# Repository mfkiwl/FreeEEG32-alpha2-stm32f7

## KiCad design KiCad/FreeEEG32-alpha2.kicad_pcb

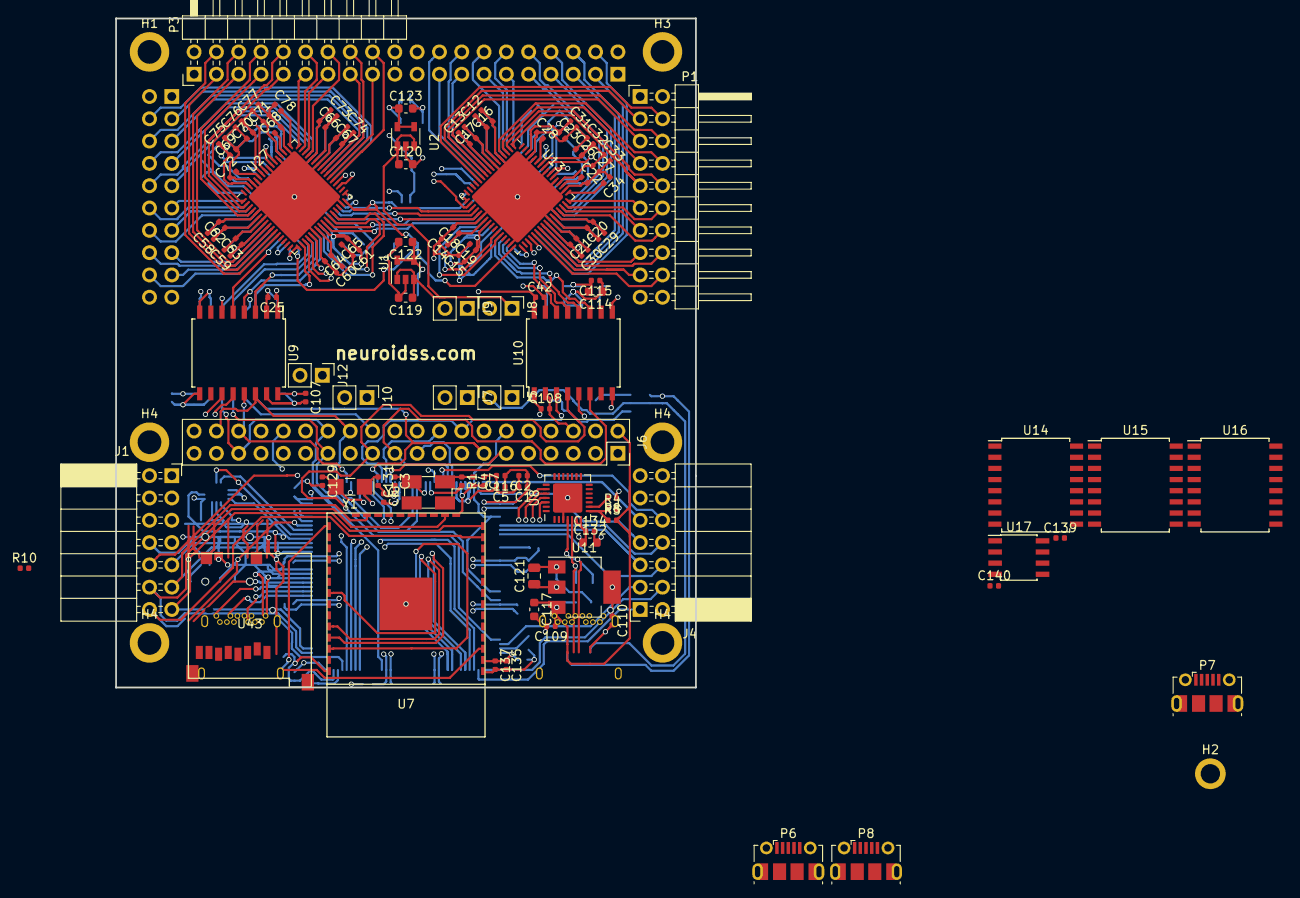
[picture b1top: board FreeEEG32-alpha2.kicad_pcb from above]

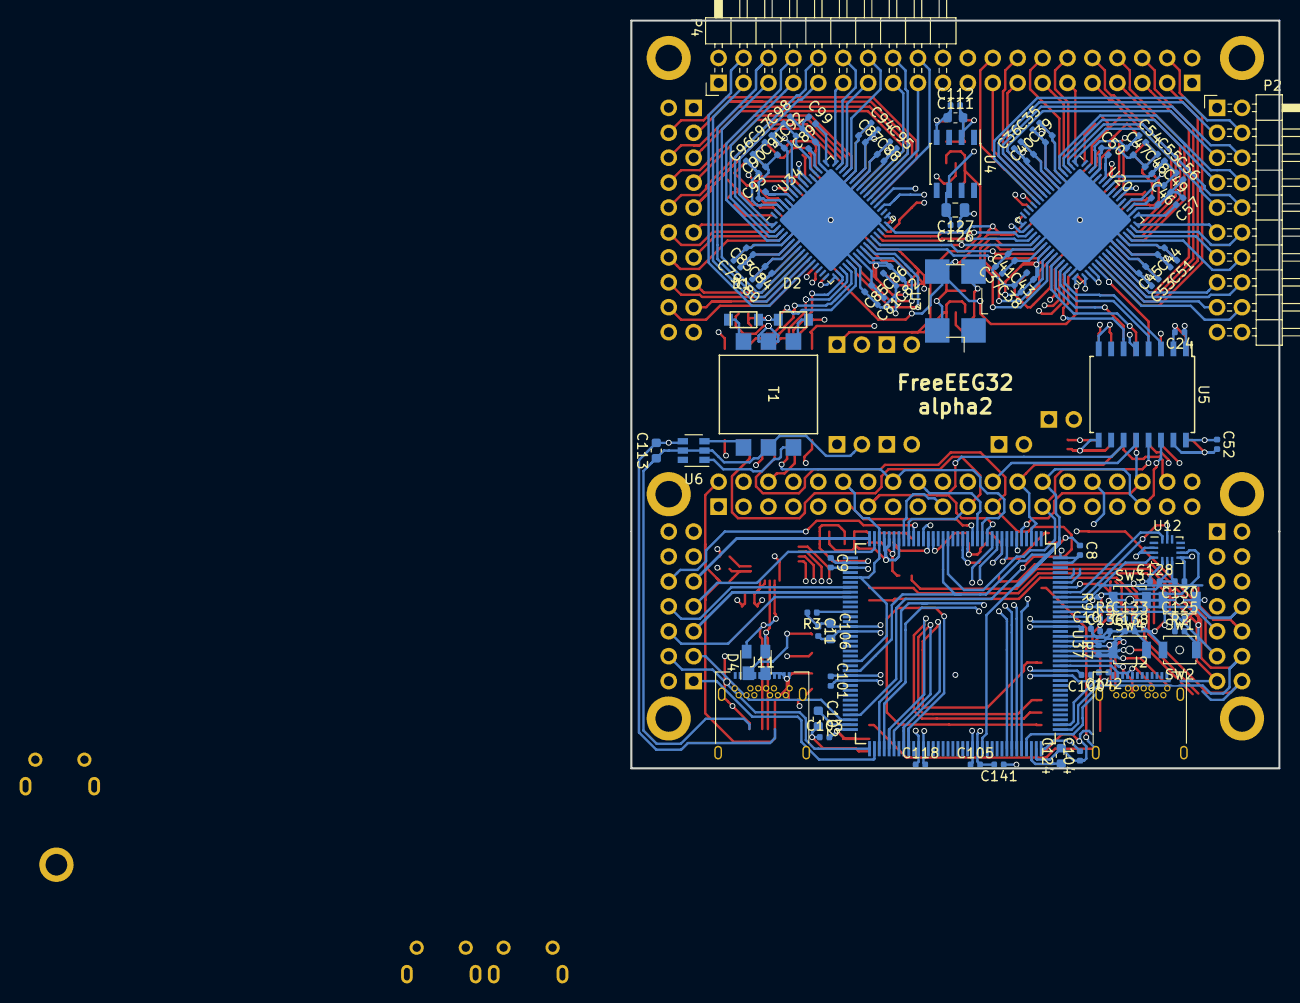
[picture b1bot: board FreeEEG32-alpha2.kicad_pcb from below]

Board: 4 copper layers, 66.0 x 76.2 mm, 209 parts (95 on the bottom side), 195 nets.

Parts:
C1, C5, C6, C7, C8, C9, C10, C11, C16, C17, C18, C19, C20, C21, C22, C23, C24, C25, C26, C27, C28, C34, C39, C40, C41, C42, C43, C44, C45, C46, C47, C48, C49, C50, C52, C57, C62, C63, C64, C65, C66, C67, C68, C69, C70, C71, C72, C78, C83, C84, C85, C86, C87, C88, C89, C90, C91, C92, C93, C99, C100, C101, C103, C104, C105, C107, C108, C109, C110, C112, C115, C118, C125, C126, C128, C130, C134, C137, C139, C140: 100n; C_0402_1005Metric
C2, C12, C13, C14, C15, C29, C30, C31, C32, C33, C35, C36, C37, C38, C51, C53, C54, C55, C56, C58, C59, C60, C61, C73, C74, C75, C76, C77, C79, C80, C81, C82, C94, C95, C96, C97, C98, C116, C135, C141, C142: 1u; C_0402_1005Metric
C3, C129: CL1; C_0402_1005Metric
C4, C131: CL2; C_0402_1005Metric
C102, C119, C120, C122, C123, C124: 2.2u; C_0603_1608Metric
C106, C132: 4.7u; C_0603_1608Metric
C111, C113, C114, C117: 10u; C_0603_1608Metric
C121, C127: 22u; C_0805_2012Metric
C133, C136, C138: 1n; C_0402_1005Metric
D1, D2: D_Schottky_SMD; SOD−123
D4: SP0503BAHTG; SOT-143
H1, H3, H4, H4#2, H4#3, H4#4: MountingHole; MountingHole_2.7mm_M2.5_ISO14580_Pad
H2: MountingHole; MountingHole_2.2mm_M2_ISO7380_Pad
J1, J4: Conn_02x07_Odd_Even; PinSocket_2x07_P2.54mm_Horizontal
J2, J11: USB_C_Receptacle-Connector_VBUS2; USB_C_Receptacle_Amphenol_12401548E4-2A
J5, J7, J8, J9, J10, J12: Conn_01x02; PinHeader_1x02_P2.54mm_Vertical
J6: Conn_02x20_Odd_Even; PinSocket_2x20_P2.54mm_Vertical
P1, P2, P3, P4: CONN_02X10; PinHeader_2x10_P2.54mm_Horizontal
P6, P7, P8: USB_OTG; USB_Micro-B_Molex-105017-0001
R1: R_EXT; R_0402_1005Metric
R2, R3: 4.7k; R_0402_1005Metric
R4: 47.5k; R_0402_1005Metric
R5: 22.1k; R_0402_1005Metric
R6, R7: 470; R_0402_1005Metric
R8: 1k; R_0402_1005Metric
R9: 12k; R_0402_1005Metric
R10: 0; R_0402_1005Metric
SW1: NRST; SW_SPST_B3U-1000P-B
SW2: BOOT0; SW_SPST_B3U-1000P-B
SW3: RST; SW_SPST_B3U-1000P-B
SW4: BOOT; SW_SPST_B3U-1000P-B
T1: da2303; 750315371
U1, U2: ADP7118AUJZ-3.3; SOT-23-5
U3: 8.192MHz; Oscillator_SMD_EuroQuartz_XO91-4Pin_7.0x5.0mm_HandSoldering
U4: ADR4525; SOIC-8_3.9x4.9mm_P1.27mm
U5, U9: ADUM1402BRWZ; SOIC-16W_7.5x10.3mm_P1.27mm
U6: SN6505B; SOT-23-6
U7: ESP32-WROOM-32; ESP32_BOARD
U8: CP2102N-28; QFN-28-1EP_5x5mm_P0.5mm_EP3.35x3.35mm
U10, U14, U15, U16: ISO7341c_spi; SOIC-16W_7.5x10.3mm_P1.27mm
U11: AMS1117-3.3; SOT-223-3_TabPin2
U12: LSM6DS3; Bosch_LGA-14_3x2.5mm_P0.5mm
U13, U20, U27, U34: AD7770; QFN-64-1EP_9x9mm_P0.5mm_EP7.5x7.5mm
U17: CAT24M01W; SOIC-8_3.9x4.9mm_P1.27mm
U37: STM32F427ZI_4side_short; LQFP-144_20x20mm_P0.5mm
U43: 473521001
Y1: 32768Hz; Crystal_SMD_EuroQuartz_EQ161-2Pin_3.2x1.5mm_HandSoldering
Y2: 8MHz; Crystal_SMD_EuroQuartz_MJ-4Pin_5.0x3.2mm_HandSoldering

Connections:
3V3_RPi: C1.2, C2.2, C5.2, C6.2, C7.1, C8.2, C9.2, C10.2, C11.2, C52.1, C100.2, C101.2, C103.2, C104.2, C105.2, C106.2, C107.1, C108.1, C110.1, C116.2, C118.2, C121.1, C128.1, C130.1, C132.1, C134.1, C135.1, C137.1, C141.2, C142.2, J1.1, J1.2, J4.13, J4.14, J6.1, J6.17, R8.1, R9.2, SW2.2, U5.16, U7.2, U8.6, U8.7, U9.16, U10.1, U11.2, U12.5, U12.8, U37.6, U37.17, U37.30, U37.32, U37.33, U37.39, U37.52, U37.62, U37.72, U37.84, U37.95, U37.108, U37.121, U37.131, U37.143, U37.144, U43.4
5V_RPi: C109.1, C117.1, J2.A4, J2.B4, J6.2, J6.4, J11.A4, J11.B4, R5.2, U11.3
/ADC1/AIN0+: P2.10, U20.2
/ADC1/AIN0-: P2.9, U20.1
/ADC1/AIN1+: P2.8, U20.4
/ADC1/AIN1-: P2.7, U20.3
/ADC1/AIN2+: P2.6, U20.10
/ADC1/AIN2-: P2.5, U20.9
/ADC1/AIN3+: P2.4, U20.12
/ADC1/AIN3-: P2.3, U20.11
/ADC1/AIN4+: P2.12, U20.47
/ADC1/AIN4-: P2.11, U20.48
/ADC1/AIN5+: P2.14, U20.45
/ADC1/AIN5-: P2.13, U20.46
/ADC1/AIN6+: P2.16, U20.39
/ADC1/AIN6-: P2.15, U20.40
/ADC1/AIN7+: P2.18, U20.37
/ADC1/AIN7-: P2.17, U20.38
/ADC1/REF_OUT: C57.2, U20.49
/ADC1/VCM: P2.2, U20.57
/ADC2/AIN0+: P3.10, U27.2
/ADC2/AIN0-: P3.9, U27.1
/ADC2/AIN1+: P3.8, U27.4
/ADC2/AIN1-: P3.7, U27.3
/ADC2/AIN2+: P3.6, U27.10
/ADC2/AIN2-: P3.5, U27.9
/ADC2/AIN3+: P3.4, U27.12
/ADC2/AIN3-: P3.3, U27.11
/ADC2/AIN4+: P3.12, U27.47
/ADC2/AIN4-: P3.11, U27.48
/ADC2/AIN5+: P3.14, U27.45
/ADC2/AIN5-: P3.13, U27.46
/ADC2/AIN6+: P3.16, U27.39
/ADC2/AIN6-: P3.15, U27.40
/ADC2/AIN7+: P3.18, U27.37
/ADC2/AIN7-: P3.17, U27.38
/ADC2/REF_OUT: C78.2, U27.49
/ADC2/VCM: P3.2, U27.57
/ADC3/AIN0+: P4.10, U34.2
/ADC3/AIN0-: P4.9, U34.1
/ADC3/AIN1+: P4.8, U34.4
/ADC3/AIN1-: P4.7, U34.3
/ADC3/AIN2+: P4.6, U34.10
/ADC3/AIN2-: P4.5, U34.9
/ADC3/AIN3+: P4.4, U34.12
/ADC3/AIN3-: P4.3, U34.11
/ADC3/AIN4+: P4.12, U34.47
/ADC3/AIN4-: P4.11, U34.48
/ADC3/AIN5+: P4.14, U34.45
/ADC3/AIN5-: P4.13, U34.46
/ADC3/AIN6+: P4.16, U34.39
/ADC3/AIN6-: P4.15, U34.40
/ADC3/AIN7+: P4.18, U34.37
/ADC3/AIN7-: P4.17, U34.38
/ADC3/REF_OUT: C99.2, U34.49
/ADC3/VCM: P4.2, U34.57
/ADC4/AIN0+: P1.10, U13.2
/ADC4/AIN0-: P1.9, U13.1
/ADC4/AIN1+: P1.8, U13.4
/ADC4/AIN1-: P1.7, U13.3
/ADC4/AIN2+: P1.6, U13.10
/ADC4/AIN2-: P1.5, U13.9
/ADC4/AIN3+: P1.4, U13.12
/ADC4/AIN3-: P1.3, U13.11
/ADC4/AIN4+: P1.12, U13.47
/ADC4/AIN4-: P1.11, U13.48
/ADC4/AIN5+: P1.14, U13.45
/ADC4/AIN5-: P1.13, U13.46
/ADC4/AIN6+: P1.16, U13.39
/ADC4/AIN6-: P1.15, U13.40
/ADC4/AIN7+: P1.18, U13.37
/ADC4/AIN7-: P1.17, U13.38
/ADC4/REF_OUT: C34.2, U13.49
/ADC4/VCM: P1.2, U13.57
AD1_CS: U5.5, U20.18
AD1_CS_ISO: J6.24, U5.12, U37.140
AD1_DCLK: U5.4, U20.29
AD1_DCLK_ISO: J6.12, J6.27, U5.13, U37.1, U37.20, U37.34, U37.41, U37.58
AD1_DOUT0: U9.3, U20.28
AD1_DOUT0_ISO: J6.26, J6.38, U9.14, U37.3
AD1_DOUT1: U9.4, U20.27
AD1_DOUT1_ISO: J6.15, J6.36, U9.13, U37.5
AD1_DOUT2: U20.26, U27.28
AD1_DOUT3: U20.25, U27.27
AD1_DRDY: U5.3, U20.30
AD1_DRDY_ISO: J6.22, J6.28, J6.35, U5.14, U37.21, U37.60, U37.96
AD1_RESET: U9.5, U13.36, U20.36, U27.36, U34.36
AD1_RESET_ISO: J6.11, U9.12, U37.15
AD1_START: C12.2, C13.2, C14.2, C15.2, C16.2, C17.2, C18.2, C19.2, C20.1, C21.1, C22.2, C23.2, C24.2, C25.2, C26.1, C27.2, C28.1, C29.1, C30.1, C31.2, C32.1, C33.2, C34.1, C35.2, C36.2, C37.2, C38.2, C39.2, C40.2, C41.2, C42.2, C43.2, C44.1, C45.1, C46.2, C47.2, C48.1, C49.2, C50.1, C51.1, C53.1, C54.2, C55.1, C56.2, C57.1, C58.2, C59.2, C60.2, C61.2, C62.2, C63.2, C64.2, C65.2, C66.1, C67.1, C68.2, C69.2, C70.1, C71.2, C72.1, C73.1, C74.1, C75.2, C76.1, C77.2, C78.1, C79.2, C80.2, C81.2, C82.2, C83.2, C84.2, C85.2, C86.2, C87.1, C88.1, C89.2, C90.2, C91.1, C92.2, C93.1, C94.1, C95.1, C96.2, C97.1, C98.2, C99.1, C111.1, C112.1, C119.2, C120.2, C122.2, C123.2, C126.1, C127.1, J9.2, P1.19, P2.19, P3.19, P4.19, U1.2, U2.2, U3.2, U4.4, U5.2, U5.8, U9.2, U9.8, U10.9, U10.15, U13.5, U13.7, U13.17, U13.22, U13.31, U13.33, U13.42, U13.44, U13.50, U13.53, U13.56, U13.60, U13.61, U13.65, U20.5, U20.7, U20.17, U20.22, U20.31, U20.33, U20.42, U20.44, U20.50, U20.53, U20.56, U20.60, U20.61, U20.65, U27.5, U27.7, U27.17, U27.22, U27.31, U27.33, U27.42, U27.44, U27.50, U27.53, U27.56, U27.60, U27.61, U27.65, U34.5, U34.7, U34.17, U34.22, U34.31, U34.33, U34.42, U34.44, U34.50, U34.53, U34.56, U34.60, U34.61, U34.65
AD1_SYNC_IN: U13.35, U20.34, U20.35, U27.35, U34.35
AD2_CS: U5.6, U27.18
AD2_CS_ISO: J6.13, U5.11, U37.12
AD2_DOUT2: U27.26, U34.28
AD2_DOUT3: U27.25, U34.27
AD3_CS: U10.14, U34.18
AD3_CS_ISO: J6.16, U10.3, U37.13
AD3_DOUT2: U13.28, U34.26
AD3_DOUT3: U13.27, U34.25
AD4_CS: U9.6, U13.18
AD4_CS_ISO: J6.18, U9.11, U37.14
AD_SCK: U10.13, U13.19, U20.19, U27.19, U34.19
AD_SCK_ISO: J6.23, U10.4, U37.69
AD_SI: U10.12, U13.20, U20.20, U27.20, U34.20
AD_SI_ISO: J6.19, U10.5, U37.29
AD_SO: U10.11, U13.21, U20.21, U27.21, U34.21
AD_SO_ISO: J6.21, U10.6, U37.28
AINREF: P1.1, P2.1, P3.1, P4.1
AVDD: C12.1, C16.1, C20.2, C23.1, C26.2, C27.1, C29.2, C31.1, C32.2, C33.1, C35.1, C39.1, C44.2, C47.1, C48.2, C49.1, C51.2, C54.1, C55.2, C56.1, C58.1, C62.1, C66.2, C69.1, C70.2, C71.1, C73.2, C75.1, C76.2, C77.1, C79.1, C83.1, C87.2, C90.1, C91.2, C92.1, C94.2, C96.1, C97.2, C98.1, C111.2, C112.2, C123.1, P1.20, P2.20, P3.20, P4.20, U2.4, U2.5, U4.2, U13.6, U13.43, U13.52, U13.58, U13.62, U20.6, U20.43, U20.52, U20.58, U20.62, U27.6, U27.43, U27.52, U27.58, U27.62, U34.6, U34.43, U34.52, U34.58, U34.62
BOOT0: R2.2, SW2.1, U37.138
BOOT1: R3.1, U37.48
CLK_SDIO: U37.122, U43.5
CMD_SDIO: U37.123, U43.3
CTS_UART_USB: U7.36, U8.23, U37.81
D+_USB_C: J2.A6, J2.B6, J6.40, U37.76
D+_USB_C_2: J11.A6, J11.B6, U8.5
D+_USB_UART: J11.A7, J11.B7, U8.4
D-_USB_C: J2.A7, J2.B7, J6.37, U37.75
DATA0_SDIO: U37.124, U43.7
DATA1_SDIO: U37.125, U43.8
DATA2_SDIO: U37.126, U43.1
DATA3_SDIO: U37.127, U43.2
DETECT_SDIO: U37.128, U43.9
EN_WIFI: C136.1, J1.14, R6.1, R9.1, R10.2, U7.3
ETH_CRS_DV: J4.8, U37.43
ETH_MDC: J4.10, U37.27
ETH_MDIO: J4.9, U37.36
ETH_REF_CLK: J4.7, U37.35
ETH_RXD0: J4.5, U37.44
ETH_RXD1: J4.6, U37.45
ETH_TXD0: J4.4, U37.73
ETH_TXD1: J4.1, U37.74
ETH_TX_EN: J4.3, U37.70
GND_ISO_RAW: C114.1, C115.1, J9.1, T1.7
GND_PWRrt1_USB_C: C1.1, C2.1, C3.2, C4.2, C5.1, C6.1, C7.2, C8.1, C9.1, C10.1, C11.1, C52.2, C100.1, C101.1, C102.2, C103.1, C104.1, C105.1, C106.1, C107.2, C108.2, C109.2, C110.2, C116.1, C117.2, C118.1, C121.2, C124.2, C125.1, C128.2, C129.2, C130.2, C131.2, C132.2, C133.2, C134.2, C135.2, C136.2, C137.2, C138.2, C141.1, C142.1, J1.3, J1.4, J2.A1, J2.B1, J4.11, J4.12, J6.6, J6.9, J6.14, J6.20, J6.25, J6.30, J6.34, J6.39, J11.A1, J11.B1, R2.1, R3.2, R4.2, SW1.2, SW3.2, SW4.2, U5.9, U5.15, U7.1, U7.15, U7.38, U7.39, U8.3, U8.29, U9.9, U9.15, U10.2, U10.8, U11.1, U12.2, U12.3, U12.6, U12.7, U37.16, U37.31, U37.38, U37.51, U37.61, U37.83, U37.94, U37.107, U37.120, U37.130, U43.6
GND_PWRrt2_USB_C: J2.A12, J2.B12, J7.2
GND_PWRrt2_USB_C_2: J11.A12, J11.B12, J12.2
GND_RAW: C113.2, J7.1, J12.1, U6.4
GPIO0_WIFI: R7.2, U7.25
I2C2_SCL: J6.5, U37.11
I2C2_SDA: J6.3, U37.10
INT1_ACC: U12.4, U37.135
INT2_ACC: U12.9, U37.132
IOVDD: C15.1, C19.1, C24.1, C25.1, C38.1, C42.1, C43.1, C61.1, C65.1, C82.1, C86.1, C122.1, U1.4, U1.5, U3.4, U5.1, U9.1, U10.16, U13.24, U13.54, U13.55, U20.24, U20.54, U20.55, U27.24, U27.54, U27.55, U34.24, U34.54, U34.55
MCO1: J6.7, U37.100
MTCK: J1.8, U7.16
MTDI: J1.12, U7.14
MTDO: J1.10, U7.23
MTMS: J1.6, U7.13
NRST: C125.2, J1.13, SW1.1, U37.25
unnamed: C3.1, U37.23, Y2.2
unnamed: C4.1, R1.1, Y2.1
unnamed: C14.1, C18.1, U13.23
unnamed: C22.1, U13.51
unnamed: C28.2, U13.59
unnamed: C37.1, C41.1, U20.23
unnamed: C46.1, U20.51
unnamed: C50.2, U20.59
unnamed: C60.1, C64.1, U27.23
unnamed: C68.1, U27.51
unnamed: C72.2, U27.59
unnamed: C81.1, C85.1, U34.23
unnamed: C89.1, U34.51
unnamed: C93.2, U34.59
unnamed: C102.1, U37.71
unnamed: C124.1, U37.106
unnamed: C129.1, U37.8, Y1.2
unnamed: C131.1, U37.9, Y1.1
unnamed: C133.1, R6.2, SW3.1
unnamed: C138.1, R7.1, SW4.1
unnamed: D1.2, T1.8
unnamed: D2.2, T1.5
unnamed: R1.2, U37.24
unnamed: R4.1, R5.1, U8.8
unnamed: R8.2, U8.9
unnamed: T1.1, U6.3
unnamed: T1.4, U6.1
RTS_UART_USB: U7.31, U8.24, U37.80
RX_UART_USB: U7.35, U8.25, U37.77
SYS_JTCK-SWCLK: J1.7, U37.109
SYS_JTDI: J1.11, U37.110
SYS_JTDO-SWO: J1.9, U37.133
SYS_JTMS-SWDIO: J1.5, U37.105
SYS_JTRST: R10.1, U37.134
TX_UART_USB: U7.34, U8.26, U37.78
USART1_RX: J6.10, U37.102
USART1_TX: J6.8, U37.101
USB_OTG_FS_DM: J6.32, U37.103
USB_OTG_FS_DP: J6.33, U37.104
V+_ISO: C119.1, C120.1, J8.1, U1.1, U1.3, U2.1, U2.3
V+_ISO_RAW: C114.2, C115.2, D1.1, D2.1, J8.2
V+_RAW: C113.1, J5.2, J10.2, T1.2, U6.2, U6.5
VBUS2_USB_C: J2.A9, J2.B9, J5.1
VBUS2_USB_C_2: J10.1, J11.A9, J11.B9
VREF: C13.1, C17.1, C21.2, C30.2, C36.1, C40.1, C45.2, C53.2, C59.1, C63.1, C67.2, C74.2, C80.1, C84.1, C88.2, C95.2, C126.2, C127.2, U4.6, U13.8, U13.41, U20.8, U20.41, U27.8, U27.41, U34.8, U34.41
XTAL: U3.3, U13.32, U20.32, U27.32, U34.32

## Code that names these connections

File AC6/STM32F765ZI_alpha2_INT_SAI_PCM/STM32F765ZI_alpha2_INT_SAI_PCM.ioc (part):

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Mcu.Name=STM32F765Z(G-I)Tx
Mcu.Package=LQFP144
Mcu.UserName=STM32F765ZITx
PA0/WKUP.GPIOParameters=GPIO_Speed
PA0/WKUP.GPIO_Speed=GPIO_SPEED_FREQ_VERY_HIGH
PA0/WKUP.Mode=SAI_B_AsyncSlave
PA0/WKUP.Signal=SAI2_SD_B
PA0/WKUP.Stacked=true
PA1.Signal=ETH_REF_CLK
PA10.Mode=Asynchronous
PA10.Signal=USART1_RX
PA11.Signal=SharedStack_PA11
PA11.Stacked=true
PA12.Signal=SharedStack_PA12
PA12.Stacked=true
PA13.Mode=Serial_Wire
PA13.Signal=SYS_JTMS-SWDIO
PA14.Mode=Serial_Wire
PA14.Signal=SYS_JTCK-SWCLK
PA15.GPIOParameters=GPIO_Speed,GPIO_PuPd
PA15.GPIO_PuPd=GPIO_NOPULL
PA15.GPIO_Speed=GPIO_SPEED_FREQ_VERY_HIGH
PA15.Signal=SharedStack_PA15
PA15.Stacked=true
PA2.Signal=SharedStack_PA2
PA2.Stacked=true
PA7.Signal=SharedStack_PA7
PA7.Stacked=true
PA8.Mode=Clock-out-1
PA8.Signal=RCC_MCO_1
PA9.Mode=Asynchronous
PA9.Signal=USART1_TX
PB10.Mode=Full_Duplex_Master
PB10.Signal=SPI2_SCK
PB11.Signal=ETH_TX_EN
PB12.Signal=ETH_TXD0
PB13.Signal=SharedStack_PB13
PB13.Stacked=true
PB14.Signal=USB_OTG_HS_DM
PB14.Stacked=true
PB15.Signal=USB_OTG_HS_DP
PB15.Stacked=true
PB3.Signal=SYS_JTDO-SWO
PB4.Signal=SPI6_MISO
PB5.Signal=SharedStack_PB5
PB5.Stacked=true
PB6.Signal=CAN2_TX
PB6.Stacked=true
PB9.GPIOParameters=GPIO_PuPd
PB9.GPIO_PuPd=GPIO_NOPULL
PB9.Mode=NSS_Signal_Hard_Output
PB9.Signal=SPI2_NSS
PC0.GPIOParameters=GPIO_Speed
PC0.GPIO_Speed=GPIO_SPEED_FREQ_VERY_HIGH
PC0.Mode=SAI_B_AsyncSlave
PC0.Signal=SAI2_FS_B
PC0.Stacked=true
PC1.Signal=ETH_MDC
PC10.GPIOParameters=GPIO_Speed
PC10.GPIO_Speed=GPIO_SPEED_FREQ_VERY_HIGH
PC10.Signal=SharedStack_PC10
PC10.Stacked=true
PC11.Signal=SharedStack_PC11
PC11.Stacked=true
PC12.Signal=SharedStack_PC12
PC12.Stacked=true
PC13.GPIOParameters=GPIO_Label
PC13.GPIO_Label=AD_START
PC13.Signal=GPIO_Output
PC2.Mode=Full_Duplex_Master
PC2.Signal=SPI2_MISO
PC3.Mode=Full_Duplex_Master
PC3.Signal=SPI2_MOSI
PC4.Signal=ETH_RXD0
PC5.Signal=ETH_RXD1
PC8.Signal=SDMMC1_D0
PC9.Signal=SharedStack_PC9
PC9.Stacked=true
PD11.GPIOParameters=GPIO_Speed
PD11.GPIO_Speed=GPIO_SPEED_FREQ_VERY_HIGH
PD11.Mode=SAI_A_SyncSlave
PD11.Signal=SAI2_SD_A
PD11.Stacked=true
PD12.Signal=SharedStack_PD12
PD12.Stacked=true
PD13.GPIOParameters=GPIO_Speed
PD13.GPIO_Speed=GPIO_SPEED_FREQ_VERY_HIGH
PD13.Signal=SAI2_SCK_A
PD2.Signal=SDMMC1_CMD
PD6.Signal=SDMMC2_CK
PD7.Signal=SDMMC2_CMD
PD8.Signal=USART3_TX
PD9.Signal=USART3_RX
PE0.GPIOParameters=GPIO_Label
PE0.GPIO_Label=AD_DRDY0
PE0.Signal=GPXTI0
PE1.GPIOParameters=GPIO_Label
PE1.GPIO_Label=AD_DRDY1
PE1.Signal=GPXTI1
PE11.GPIOParameters=GPIO_PuPd
PE11.GPIO_PuPd=GPIO_NOPULL
PE11.Mode=NSS_Signal_Hard_Output
PE11.Signal=SPI4_NSS
PE12.Mode=Full_Duplex_Master
PE12.Signal=SPI4_SCK
PE13.Mode=Full_Duplex_Master
PE13.Signal=SPI4_MISO
PE14.Mode=Full_Duplex_Master
PE14.Signal=SPI4_MOSI
PE2.GPIOParameters=GPIO_Label
PE2.GPIO_Label=AD_DRDY2
PE2.Signal=GPXTI2
PE3.GPIOParameters=GPIO_Speed
PE3.GPIO_Speed=GPIO_SPEED_FREQ_VERY_HIGH
PE3.Mode=SAI_B_AsyncSlave
PE3.Signal=SAI1_SD_B
PE4.GPIOParameters=GPIO_Speed
PE4.GPIO_Speed=GPIO_SPEED_FREQ_VERY_HIGH
PE4.Mode=SAI_A_AsyncSlave
PE4.Signal=SAI1_FS_A
PE5.GPIOParameters=GPIO_Speed
PE5.GPIO_Speed=GPIO_SPEED_FREQ_VERY_HIGH
PE5.Mode=SAI_A_AsyncSlave
PE5.Signal=SAI1_SCK_A
PE6.GPIOParameters=GPIO_Speed
PE6.GPIO_Speed=GPIO_SPEED_FREQ_VERY_HIGH
PE6.Mode=SAI_A_AsyncSlave
PE6.Signal=SAI1_SD_A
PF0.Signal=I2C2_SDA
PF1.Signal=I2C2_SCL
PF10.GPIOParameters=GPIO_Speed,GPIO_Label
PF10.GPIO_Label=AD_RESET
PF10.GPIO_Speed=GPIO_SPEED_FREQ_VERY_HIGH
PF10.Signal=SharedStack_PF10
PF10.Stacked=true
PF12.Signal=GPIO_Input
PF2.GPIOParameters=GPIO_Speed,GPIO_Label
PF2.GPIO_Label=SPI2_NSS_AD1
PF2.GPIO_Speed=GPIO_SPEED_FREQ_VERY_HIGH
PF2.Signal=GPIO_Output
PF3.GPIOParameters=GPIO_Speed,GPIO_Label
PF3.GPIO_Label=SPI2_NSS_AD2
PF3.GPIO_Speed=GPIO_SPEED_FREQ_VERY_HIGH
PF3.Signal=GPIO_Output
PF4.GPIOParameters=GPIO_Speed,GPIO_Label
PF4.GPIO_Label=SPI2_NSS_AD3
PF4.GPIO_Speed=GPIO_SPEED_FREQ_VERY_HIGH
PF4.Signal=GPIO_Output
PF5.GPIOParameters=GPIO_Speed,PinState,GPIO_Label
PF5.GPIO_Label=SPI2_NSS_AD4
PF5.GPIO_Speed=GPIO_SPEED_FREQ_VERY_HIGH
PF5.PinState=GPIO_PIN_RESET
PF5.Signal=GPIO_Output
PF6.Mode=Asynchronous
PF6.Signal=UART7_RX
PF7.Mode=Asynchronous
PF7.Signal=UART7_TX
PF8.GPIOParameters=GPIO_Speed
PF8.GPIO_Speed=GPIO_SPEED_FREQ_VERY_HIGH
PF8.Mode=SAI_B_AsyncSlave
PF8.Signal=SAI1_SCK_B
PF9.GPIOParameters=GPIO_Speed
PF9.GPIO_Speed=GPIO_SPEED_FREQ_VERY_HIGH
PF9.Mode=SAI_B_AsyncSlave
PF9.Signal=SAI1_FS_B
PG0.Signal=GPIO_Input
PG1.Signal=GPIO_Input
PG10.Signal=SDMMC2_D1
PG10.Stacked=true
PG11.Signal=SDMMC2_D2
PG12.Signal=SDMMC2_D3
PG13.Signal=SPI6_SCK
PG2.Signal=GPIO_Input
PG3.Signal=GPIO_Input
PG4.Signal=GPIO_Input
PG5.Signal=GPIO_Input
PG6.Signal=GPIO_Input
PG8.Signal=SPI6_NSS
PG9.Signal=SDMMC2_D0
RCC.HSE_VALUE=8192000
RCC.SYSCLKFreq_VALUE=216000000
RCC.SYSCLKSource=RCC_SYSCLKSOURCE_PLLCLK
board=custom
